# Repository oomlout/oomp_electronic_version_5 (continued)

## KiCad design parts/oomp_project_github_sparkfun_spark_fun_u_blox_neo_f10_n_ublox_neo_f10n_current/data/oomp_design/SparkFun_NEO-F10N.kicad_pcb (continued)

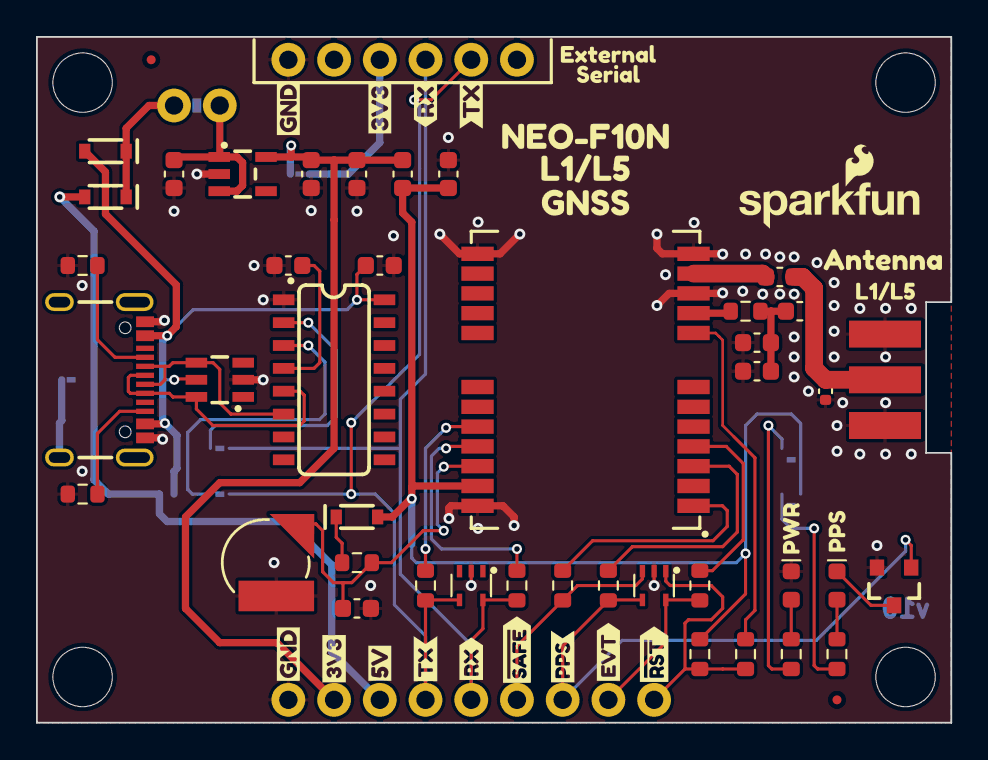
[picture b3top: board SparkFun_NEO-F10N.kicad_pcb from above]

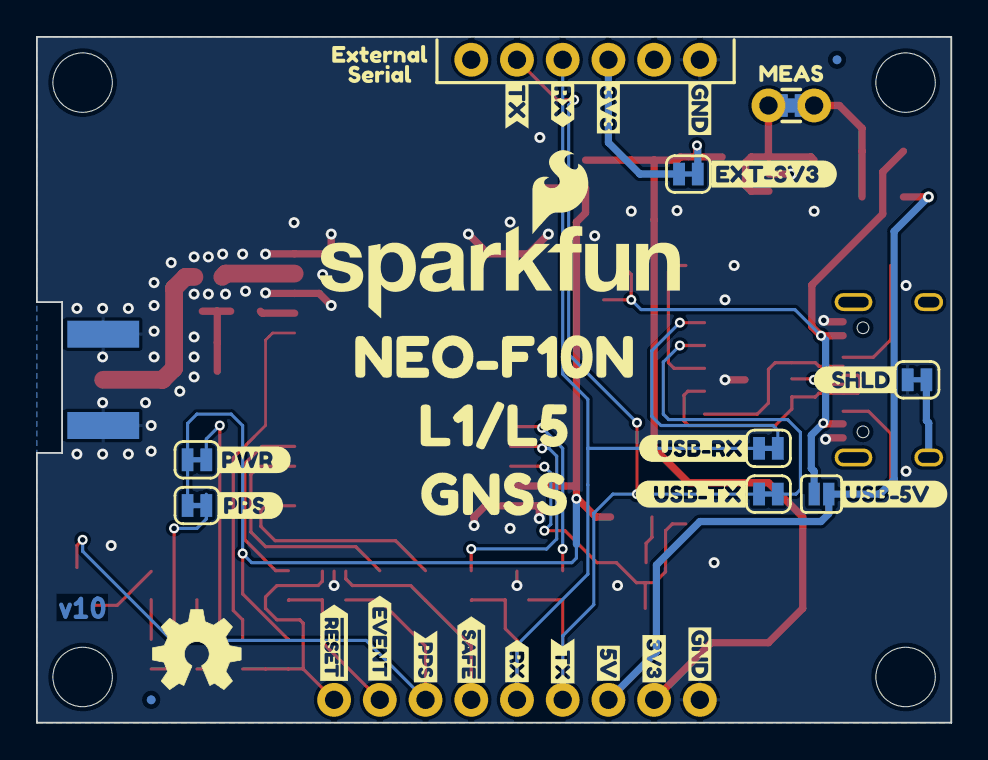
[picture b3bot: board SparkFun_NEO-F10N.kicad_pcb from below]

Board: 2 copper layers, 50.8 x 38.1 mm, 110 parts (37 on the bottom side), 39 nets.

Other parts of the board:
Ref**: Val**; OSHW_Logo_5mm
kibuzzard-64C2E6A3: G***; kibuzzard-64C2E6A3
kibuzzard-64C2E6BD: G***; kibuzzard-64C2E6BD
kibuzzard-64C2EB16: G***; kibuzzard-64C2EB16
kibuzzard-64D296AE: G***; kibuzzard-64D296AE
kibuzzard-64E773DA, kibuzzard-64E773DA#2: G***; kibuzzard-64E773DA
kibuzzard-64E774E1: G***; kibuzzard-64E774E1
kibuzzard-64E774E7: G***; kibuzzard-64E774E7
kibuzzard-64E774EF: G***; kibuzzard-64E774EF
kibuzzard-64E774F5: G***; kibuzzard-64E774F5
kibuzzard-654D4A62: G***; kibuzzard-654D4A62
kibuzzard-654D4E9F: G***; kibuzzard-654D4E9F
kibuzzard-654D4E65: G***; kibuzzard-654D4E65
kibuzzard-654D4E82: G***; kibuzzard-654D4E82
kibuzzard-654D4EBD: G***; kibuzzard-654D4EBD
kibuzzard-654D22C2, kibuzzard-654D22C2#2: G***; kibuzzard-654D22C2
kibuzzard-654D22ED: G***; kibuzzard-654D22ED
kibuzzard-654D22FF: G***; kibuzzard-654D22FF
kibuzzard-654D24A3: G***; kibuzzard-654D24A3
kibuzzard-654D24AA: G***; kibuzzard-654D24AA
kibuzzard-654D24CA: G***; kibuzzard-654D24CA
kibuzzard-654D232B: G***; kibuzzard-654D232B
kibuzzard-654D2357: G***; kibuzzard-654D2357
kibuzzard-655A6C20: G***; kibuzzard-655A6C20
kibuzzard-655A6C73: G***; kibuzzard-655A6C73
kibuzzard-655A6CC4: G***; kibuzzard-655A6CC4
kibuzzard-655A6CE2: G***; kibuzzard-655A6CE2
kibuzzard-6542D1F0: G***; kibuzzard-6542D1F0
kibuzzard-6542D1FC: G***; kibuzzard-6542D1FC
kibuzzard-6542D20F: G***; kibuzzard-6542D20F
kibuzzard-6542D208: G***; kibuzzard-6542D208
kibuzzard-6598A013: G***; kibuzzard-6598A013
kibuzzard-6598A076: G***; kibuzzard-6598A076
kibuzzard-65989F3D: G***; kibuzzard-65989F3D
kibuzzard-65989F89: G***; kibuzzard-65989F89
kibuzzard-65989F92: G***; kibuzzard-65989F92
kibuzzard-650880E6: G***; kibuzzard-650880E6
kibuzzard-659876FC: G***; kibuzzard-659876FC
kibuzzard-6598770D: G***; kibuzzard-6598770D
kibuzzard-6598978C: G***; kibuzzard-6598978C
kibuzzard-6598994F, kibuzzard-6598994F#2: G***; kibuzzard-6598994F
kibuzzard-65989731, kibuzzard-65989731#2: G***; kibuzzard-65989731
kibuzzard-65989781: G***; kibuzzard-65989781
kibuzzard-65989942, kibuzzard-65989942#2: G***; kibuzzard-65989942

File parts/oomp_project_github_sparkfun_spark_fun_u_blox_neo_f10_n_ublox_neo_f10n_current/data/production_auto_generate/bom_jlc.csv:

Comment,Designator,Footprint,LCSC Part #
 PESD0402,D6,SparkFun-Capacitor:C_0402_1005Metric,C316059
0.1uF,"C1,C2,C4,C12,C13,C16",SparkFun-Capacitor:C_0603_1608Metric,C14663
1.0uF,"C3,C8",SparkFun-Capacitor:C_0603_1608Metric,C5673
10,R3,SparkFun-Resistor:R_0603_1608Metric,C22859
10k,R12,SparkFun-Resistor:R_0603_1608Metric,C98220
1k,R7,SparkFun-Resistor:R_0603_1608Metric,C2907002
2.2k,R5,SparkFun-Resistor:R_0603_1608Metric,C4190
30Ohm,L2,SparkFun-Capacitor:C_0603_1608Metric,
33,"R15,R16,R29,R30,R31,R34",SparkFun-Resistor:R_0603_1608Metric,C23140
33nH,L1,SparkFun-Capacitor:C_0603_1608Metric,
4.7k,R4,SparkFun-Resistor:R_0603_1608Metric,C23162
47pF,"C6,C7",SparkFun-Capacitor:C_0603_1608Metric,C105622
5.1k,"R1,R2",SparkFun-Resistor:R_0603_1608Metric,C23186
6.8mm_ML414H,BT1,SparkFun-Battery:ML414H_IV01E,
AP2112K-3.3,U2,SparkFun-Semiconductor-Standard:SOT23-5,
BSS138,Q1,SparkFun-Semiconductor-Standard:SOT23-3,C52895
CH340C,U8,SparkFun-Semiconductor-Standard:SO-16,C84681
Conn_01x06,J4,SparkFun-Connector:1x06,C37208
Conn_01x09,J2,SparkFun-Connector:1x09,C2932701
DT1042-04SO,U1,SparkFun-Semiconductor-Standard:SOT23-6,C460064
Measure,JP5,SparkFun-Jumper:Jumper_2_PTH_SMD_Combo-NC,
NEO-F10N,U3,SparkFun-GPS:NEO-M9N_M8T_M8U_D9S_F9P_F10N,
PESD3V3L4UG,"D2,D3",SparkFun-Semiconductor-Standard:SOT-353,C70500
PMEG4005EJ,"D5,D7,D8",SparkFun-Semiconductor-Standard:SOD-323,
Red,D1,SparkFun-LED:LED_0603_1608Metric_Red,
USB_C_Receptacle,J1,SparkFun-Connector:USB-C_16,C2765186
Val**,J5,SparkFun-Connector:SMA_Edge,
Yellow,D4,SparkFun-LED:LED_0603_1608Metric_Yellow,
~,U7,SparkFun-Aesthetic:Ordering_Instructions,
~,"JP1,JP2,JP3,JP4,JP7,JP8",SparkFun-Jumper:Jumper_2_NC_Trace,
~,JP6,SparkFun-Jumper:Jumper_2_NO,

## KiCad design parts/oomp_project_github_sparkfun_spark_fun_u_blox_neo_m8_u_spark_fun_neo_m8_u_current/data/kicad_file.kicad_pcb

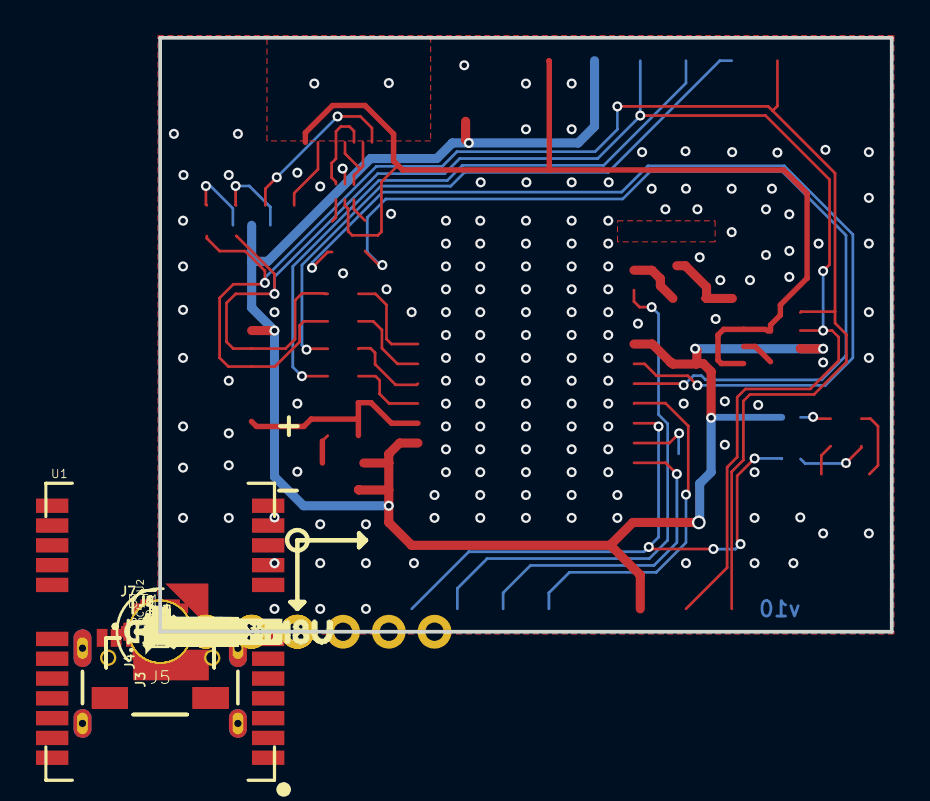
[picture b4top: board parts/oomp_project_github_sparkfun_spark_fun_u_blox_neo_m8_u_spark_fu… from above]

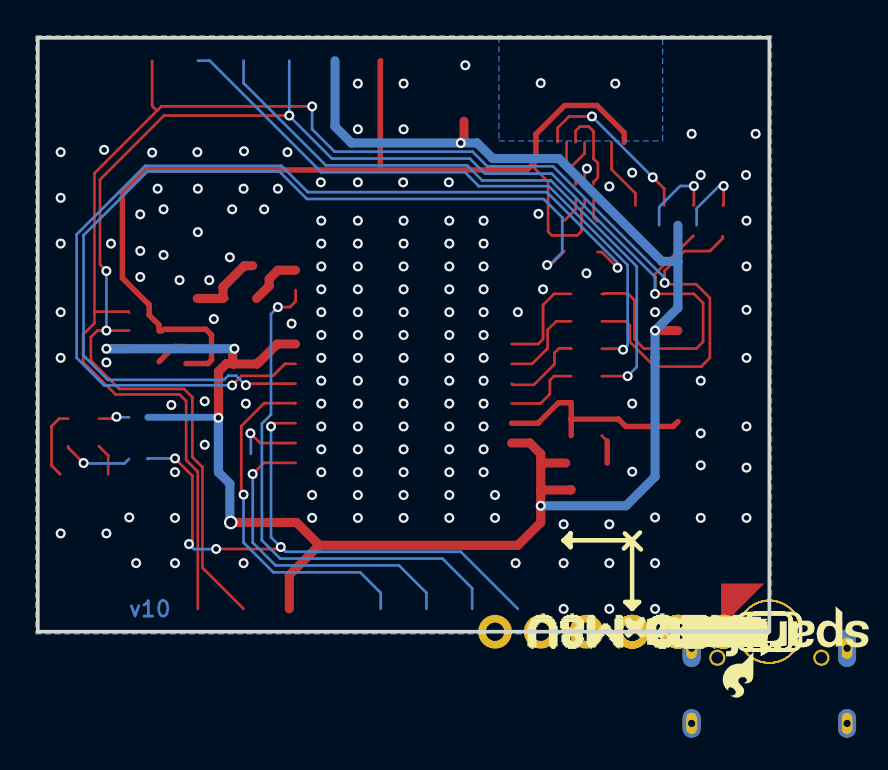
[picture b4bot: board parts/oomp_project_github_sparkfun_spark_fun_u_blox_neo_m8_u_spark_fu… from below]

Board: 2 copper layers, 40.6 x 33.0 mm, 98 parts (31 on the bottom side), 36 nets.

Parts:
BT1: 6.8MM_COIN_CELL; ML414H_IV01E
C1, C2, C4: 1.0uF; 0603
C3: 47pF; 0603
C5: 0.1uF; 0603
D1: RED; LED-0603
D2: BLUE; LED-0603
D3: 0.5A/40V/420mV; SOD-323
D4: PRTR5V0U2F; SOT886
FB1: 30Ω/1.8A; 0603
FRAME1: FRAME-LETTER; CREATIVE_COMMONS
J1, J2: 1X04_NO_SILK
J3, J4: Qwiic Right Angle; JST04_1MM_RA
J5: USB-C-16P-2LAYER-PADS
J6: 1X07_NO_SILK
J7: U.FL
JP1: JUMPER-SMT_3_2-NC_TRACE_SILK; SMT-JUMPER_3_2-NC_TRACE_SILK
JP2, JP3: JUMPER-SMT_2_NC_TRACE_SILK; SMT-JUMPER_2_NC_TRACE_SILK
JP4: JUMPER-SMT_2_NO_SILK; SMT-JUMPER_2_NO_SILK
JP5, JP6, JP7, JP8: FIDUCIALUFIDUCIAL; MICRO-FIDUCIAL
JP9, JP10, JP11, JP12: STAND-OFF
LOGO1: OSHW-LOGOMINI; OSHW-LOGO-MINI
LOGO2: SFE_LOGO_NAME_FLAME.1_INCH; SFE_LOGO_NAME_FLAME_.1
R1, R2: 27; 0603
R3: 100k; 0603
R4, R7: 2.2k; 0603
R5, R6, R14: 1k; 0603
R8, R9, R10, R11: 33; 0603
R12, R13: 5.1k; 0603
R15: 10; 0603
U1: U-BLOX_MEO-M8U; NEO-M9N_M8T_M8U
U2: 3.3V; SOT23-5
U$1, U$4: SDA-[)
U$2: INT1
U$3, U$5: SCL-[)
U$6, U$7, U$60, U$61: 3V3-04
U$8, U$9, U$62, U$63: GND-04
U$10: I_SUPER2_C-()-03
U$11: SPI1
U$12, U$52: PPS0
U$13, U$16: X1
U$14: QWIIC_4MM
U$15, U$34: NEO#M8U0
U$17: PWR1
U$18: PWR-()-03
U$19, U$20: 5V
U$21, U$27: Y2
U$22: U#BLOX3
U$23, U$24: CS#-_]
U$25: ANT0
U$26, U$31: RX#MOSI3
U$28, U$30: Z0
U$29, U$37: TX#MISO1
U$32: INT0
U$33: SFE_LOGO_FLAME_.1
U$35, U$36: #RST3
U$38, U$41: SCK-(]-04
U$39, U$40: #SAFE1
U$43, U$44: PPS5

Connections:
3.3V: C4.1, C5.2, D3.A, J1.2, J3.2, J4.2, J6.3, JP1.2, JP2.2, R3.2, U1.7, U1.23, U2.5
5V: C2.1, D4.5, J5.VBUS1, J5.VBUS2, J6.2, U2.1, U2.3
ANT_VCC: C3.1, FB1.2, R15.1
D+: D4.4, R1.1
D-: D4.6, R2.1
D_SEL: JP4.2, U1.2
EXT_INT: J2.4, U1.4
GND: BT1.-, C1.2, C2.2, C3.2, C4.2, C5.1, D1.C, D2.C, D4.2, J1.1, J3.1, J4.1, J5.GND, J5.GND2, J6.1, J7.1, J7.2, JP4.1, R3.1, R12.1, R13.1, U1.10, U1.12, U1.13, U1.24, U2.2
GPS_ANT1: FB1.1, J7.FEED, U1.11
unnamed: JP2.1, R5.2
unnamed: D2.A, R6.1
unnamed: R8.1, U1.18
unnamed: JP3.1, R6.2
unnamed: JP1.1, R7.2
unnamed: D3.C, R14.2
unnamed: J5.B5, R12.2
unnamed: JP1.3, R4.2
unnamed: J5.A5, R13.2
unnamed: D1.A, R5.1
unnamed: R1.2, U1.6
unnamed: R2.2, U1.5
unnamed: R9.1, U1.19
unnamed: R10.1, U1.20
unnamed: R11.1, U1.21
PPS: J2.1, JP3.2, U1.3
RXI/MOSI: J6.5, R11.2
SCL/SCK: J1.4, J3.4, J4.4, J6.7, R4.1, R9.2
SDA/~CS: J1.3, J3.3, J4.3, J6.4, R7.1, R8.2
SHIELD: J5.SHLD1, J5.SHLD2, J5.SHLD3, J5.SHLD4
TP2/~SAFE: J2.3, U1.1
TXO/MISO: J6.6, R10.2
USB_D+: D4.3, J5.A6, J5.B6
USB_D-: D4.1, J5.A7, J5.B7
VDD: R15.2, U1.9
V_BATT: BT1.+, C1.1, R14.1, U1.22
~RESET: J2.2, U1.8

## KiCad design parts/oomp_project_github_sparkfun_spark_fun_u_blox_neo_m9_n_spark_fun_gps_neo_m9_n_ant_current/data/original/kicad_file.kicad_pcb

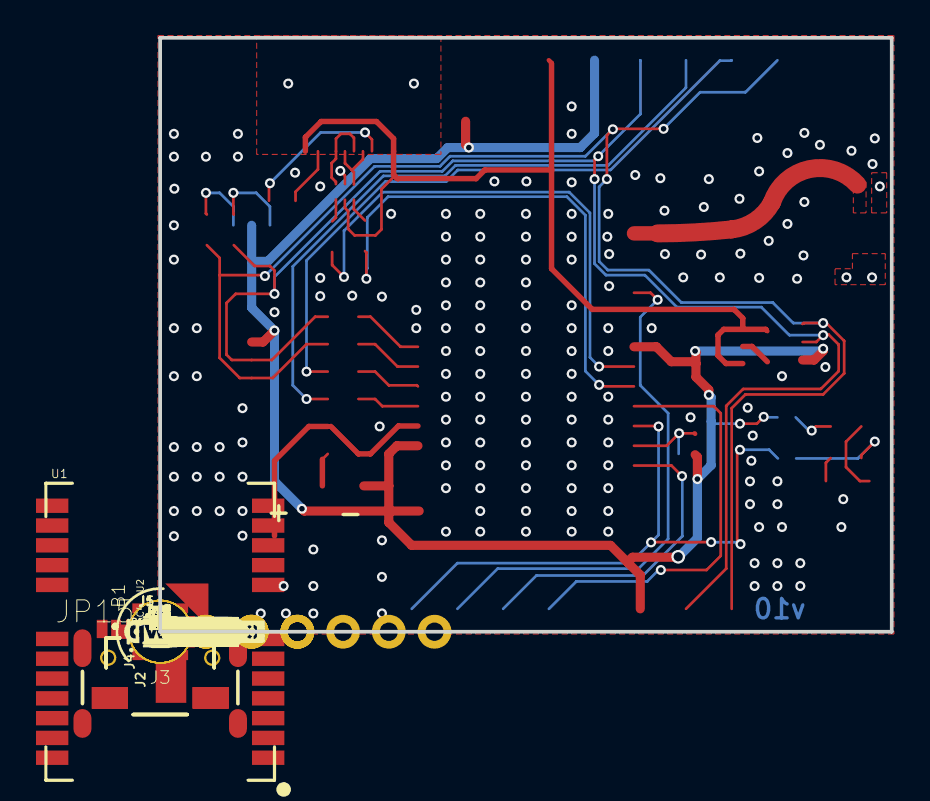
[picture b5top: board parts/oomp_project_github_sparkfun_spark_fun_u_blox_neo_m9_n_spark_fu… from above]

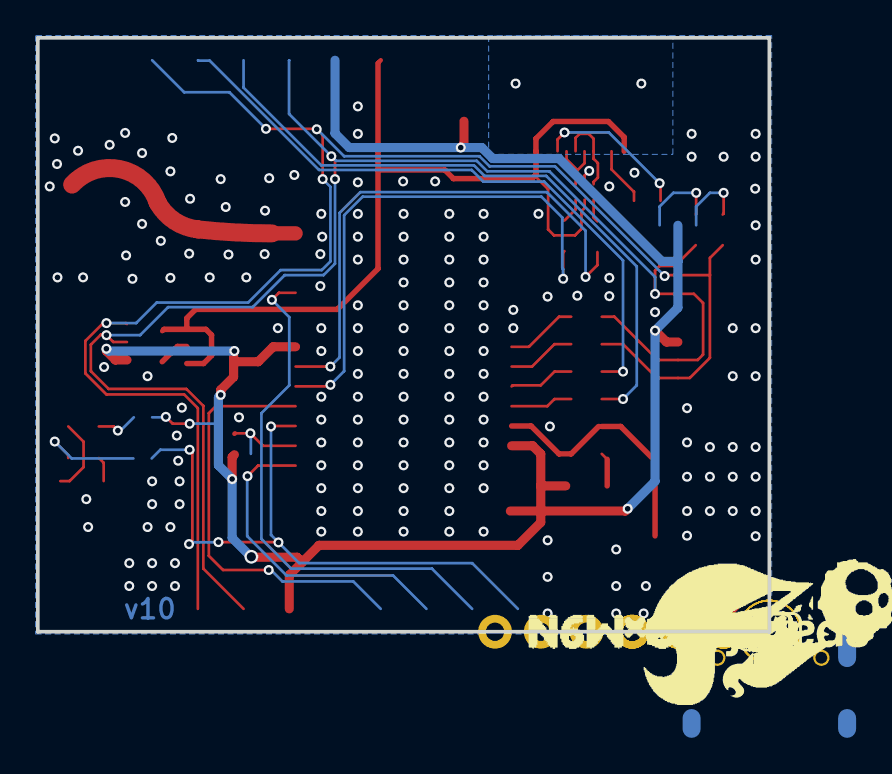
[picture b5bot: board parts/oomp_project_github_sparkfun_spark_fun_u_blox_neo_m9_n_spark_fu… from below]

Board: 2 copper layers, 40.6 x 33.0 mm, 89 parts (30 on the bottom side), 34 nets.

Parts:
B1: 6.8MM_COIN_CELL; ML414H_IV01E
C3, C4, C6: 1.0uF; 0603
C5: 0.1uF; 0603
D2: 0.5A/40V/420mV; SOD-323
D3: PRTR5V0U2F; SOT886
FRAME1: FRAME-LETTER; CREATIVE_COMMONS
J1: 1X07_NO_SILK
J2, J4: Qwiic Right Angle; JST04_1MM_RA
J3: USB-C-16P
J5: 1X04_NO_SILK
JP5: JUMPER-SMT_3_2-NC_TRACE_SILK; SMT-JUMPER_3_2-NC_TRACE_SILK
JP15: 1X04_NO_SILK
JP21, JP61, JP71, JP81: FIDUCIALUFIDUCIAL; MICRO-FIDUCIAL
JP31, JP41, JP91, JP101: STAND-OFF
LED1: BLUE; LED-0603
LED2: RED; LED-0603
LOGO1: OSHW-LOGOMINI; OSHW-LOGO-MINI
LOGO2: SFE_LOGO_NAME_FLAME.1_INCH; SFE_LOGO_NAME_FLAME_.1
PPS0: JUMPER-SMT_2_NC_TRACE_SILK; SMT-JUMPER_2_NC_TRACE_SILK
PWR\0: JUMPER-SMT_2_NC_TRACE_SILK; SMT-JUMPER_2_NC_TRACE_SILK
R1, R5, R11: 1k; 0603
R2, R3, R4, R6: 33; 0603
R7, R8: 2.2k; 0603
R9, R10: 27; 0603
R12, R13: 5.1k; 0603
R15: 100k; 0603
R16: 10k; 0402
SPI0: JUMPER-SMT_2_NO_SILK; SMT-JUMPER_2_NO_SILK
U1: U-BLOX_NEO-M9N; NEO-M9N
U2: 3.3V; SOT23-5
U$1, U$4: SDA-[)
U$2: NEO#M9N1
U$3, U$5: SCL-[)
U$6, U$7, U$60, U$61: 3V3-04
U$8, U$9, U$62, U$63: GND-04
U$10: I_SUPER2_C-()-03
U$11: SPI1
U$12, U$52: PPS0
U$13: ANT0
U$14: QWIIC_4MM
U$15, U$16: INT8
U$17: PWR1
U$18: PWR-()-03
U$19, U$20: 5V
U$21: NEO_GPS_BOARD_SILK_FINAL#03#JPG
U$22: U#BLOX3
U$23, U$24: CS#-_]
U$26: RX#MOSI2
U$31: RX#MOSI3
U$34: TX#MISO0
U$35, U$36: #RST3
U$37: TX#MISO1
U$38, U$41: SCK-(]-04
U$39, U$40: #SAFE1
U$43, U$44: PPS5
Y1: GPS_CHIP_ANTENNAW3011; W3011

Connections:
3.3V: C4.1, C5.2, D2.A, J1.3, J2.2, J4.2, J5.2, JP5.2, PWR\0.2, R15.2, R16.2, U1.7, U1.23, U2.5
5V: C6.1, D3.5, J1.2, J3.VBUS1, J3.VBUS2, U2.1, U2.3
BACKUP: B1.+, C3.1, R5.1, U1.22
D+: D3.4, R9.1
D-: D3.6, R10.1
D_SEL: R16.1, SPI0.2, U1.2
GND: B1.-, C3.2, C4.2, C5.1, C6.2, D3.2, J1.1, J2.1, J3.GND, J3.GND2, J4.1, J5.1, LED1.C, LED2.C, R12.1, R13.1, R15.1, SPI0.1, U1.10, U1.12, U1.13, U1.24, U2.2, Y1.2, Y1.3
GPS_ANT1: U1.11, Y1.1
INT: JP15.1, U1.4
unnamed: PWR\0.1, R1.2
unnamed: LED1.A, R11.1
unnamed: PPS0.1, R11.2
unnamed: JP5.1, R8.2
unnamed: D2.C, R5.2
unnamed: J3.B5, R12.2
unnamed: JP5.3, R7.2
unnamed: J3.A5, R13.2
unnamed: LED2.A, R1.1
unnamed: R9.2, U1.6
unnamed: R10.2, U1.5
PPS: JP15.4, PPS0.2, U1.3
RXI/MOSI: J1.5, R6.2
RXLV: R6.1, U1.21
SCL/SCK: J1.7, J2.4, J4.4, J5.4, R4.2, R7.1
SCL_LV: R4.1, U1.19
SDA/~CS: J1.4, J2.3, J4.3, J5.3, R2.2, R8.1
SDA_LV: R2.1, U1.18
SHLD: J3.SHLD1, J3.SHLD2, J3.SHLD3, J3.SHLD4, J3.SHLD5, J3.SHLD6, J3.SHLD7, J3.SHLD8
TXLV: R3.1, U1.20
TXO/MISO: J1.6, R3.2
USB_D+: D3.3, J3.A6, J3.B6
USB_D-: D3.1, J3.A7, J3.B7
~RESET: JP15.3, U1.8
~SAFE: JP15.2, U1.1
